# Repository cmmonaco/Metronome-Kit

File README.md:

# Metronome Kit

This barebones metronome was designed as a kit which was sold on Club Jameco (discontinued). Features include a small speaker, flashing LED, and the ability to switch between several different time signature options. The kit includes a three digit seven-segment display to display the speed in beats per minute and runs off of three AA batteries.

Details for the build can be found on [Instructables](https://www.instructables.com/id/Electronic-Metronome/). 

## Bill of Materials
- ATmega328p Microcontroller (Jameco #2139111)
- IC Socket (Jameco #112300)
- 150 Ohm Resistor (Jameco #690662)
- 10k Ohm Resistor (Jameco #691104)
- 0.1 uF Capacitor (Jameco #151116)
- Three Digit Seven Segment Display (Jameco #1956493)
- Red 5mm LED (Jameco #333973)
- Tactile Switch (3x) (Jameco #119011)
- Piezo Speaker (Jameco #1874543)
- ISP Header (Jameco #115035)
- 3xAA Battery Holder with Switch (Jameco #216144)
- AA Battery (3x)
- Velcro (Optional)

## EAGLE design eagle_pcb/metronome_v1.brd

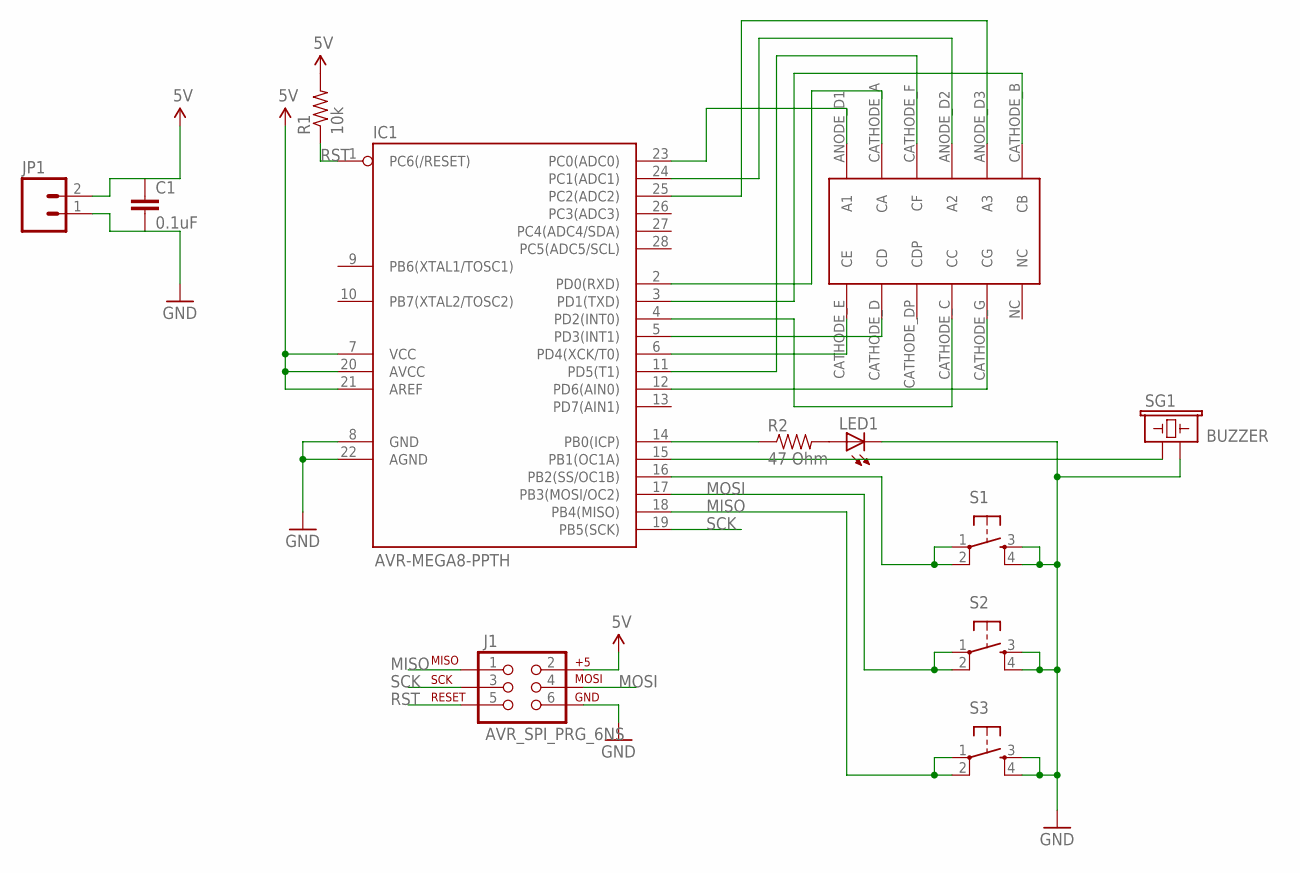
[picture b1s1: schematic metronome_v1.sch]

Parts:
C1: 0.1uF; CAP-PTH-SMALL
IC1: AVR-MEGA8-PPTH; DIL28-3
J1: AVR_SPI_PRG_6NS; 2X3-NS
JP1: M02PTH3; 1X02_LONGPADS
LED1: LED5MM
R1: 10k; AXIAL-0.3
R2: 47 Ohm; AXIAL-0.3
S1, S2, S3: TAC_SWITCHPTH; TACTILE-PTH
SG1: BUZZER; BUZZER-762MM
U$1: 7-SEGMENT-3DIGIT-LTC516R; 7-SEGMENT-3DIGIT-LTC561R

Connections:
5V: C1.1, IC1.7 (VCC), IC1.20 (AVCC), IC1.21 (AREF), J1.2, JP1.2, R1.P$2 (2)
GND: C1.2, IC1.8 (GND), IC1.22 (AGND), J1.6, JP1.1, LED1.K (C), S1.3, S1.4, S2.3, S2.4, S3.3, S3.4, SG1.P$2 (2)
MISO: IC1.18 (PB4(MISO)), J1.1, S3.1, S3.2
MOSI: IC1.17 (PB3(MOSI/OC2)), J1.4, S2.1, S2.2
unnamed: LED1.A, R2.P$2 (2)
unnamed: IC1.14 (PB0(ICP)), R2.P$1 (1)
unnamed: IC1.2 (PD0(RXD)), U$1.CATHODE_A (CA)
unnamed: IC1.3 (PD1(TXD)), U$1.CATHODE_B (CB)
unnamed: IC1.15 (PB1(OC1A)), SG1.P$1 (1)
unnamed: IC1.16 (PB2(SS/OC1B)), S1.1, S1.2
unnamed: IC1.4 (PD2(INT0)), U$1.CATHODE_C (CC)
unnamed: IC1.5 (PD3(INT1)), U$1.CATHODE_D (CD)
unnamed: IC1.6 (PD4(XCK/T0)), U$1.CATHODE_E (CE)
unnamed: IC1.11 (PD5(T1)), U$1.CATHODE_F (CF)
unnamed: IC1.12 (PD6(AIN0)), U$1.CATHODE_G (CG)
unnamed: IC1.23 (PC0(ADC0)), U$1.ANODE_D1 (A1)
unnamed: IC1.24 (PC1(ADC1)), U$1.ANODE_D2 (A2)
unnamed: IC1.25 (PC2(ADC2)), U$1.ANODE_D3 (A3)
RST: IC1.1 (PC6(/RESET)), J1.5, R1.P$1 (1)
SCK: IC1.19 (PB5(SCK)), J1.3

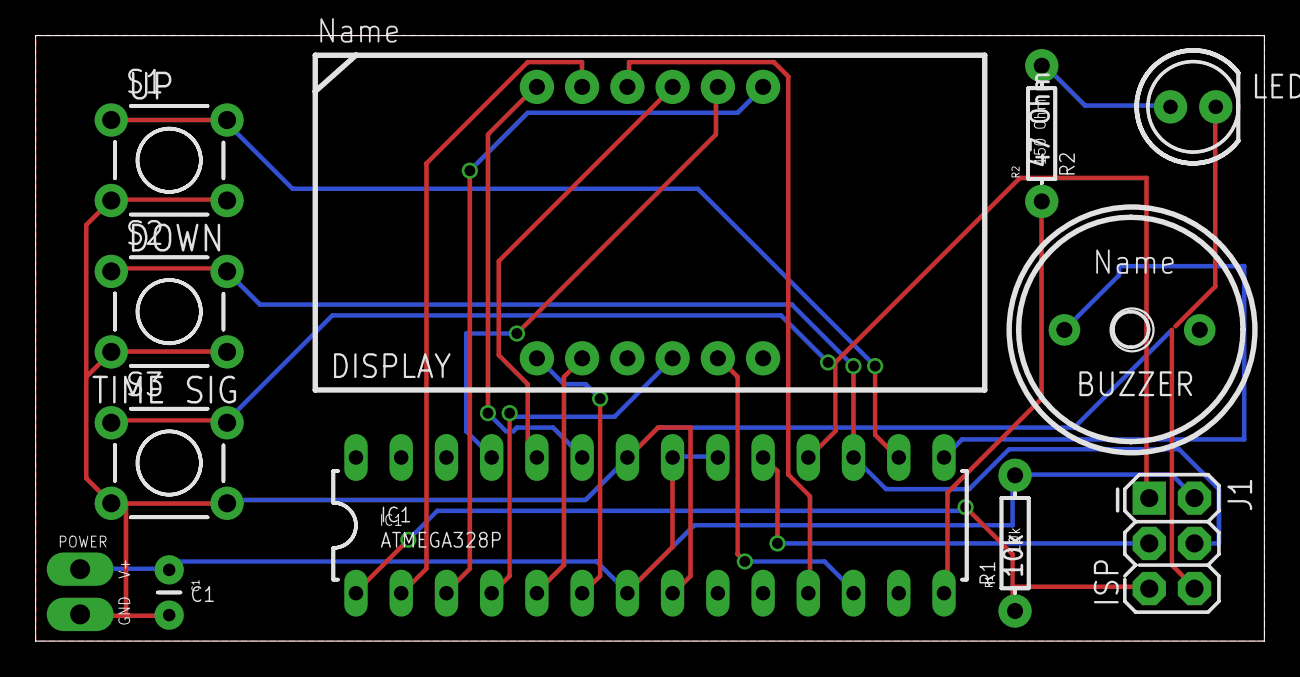
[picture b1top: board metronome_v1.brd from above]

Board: 2 copper layers, 69.0 x 34.0 mm, 12 parts (0 on the bottom side), 20 nets.

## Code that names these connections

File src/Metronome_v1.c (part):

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#define MAX_SPEED              250   //Max metronome speed in BPM
#define MIN_SPEED              30    //Min metronome speed in BPM

#define DISP_CATH_PORT         PORTD //The Display cathodes are connected to pins PD0-PD6
#define DISP_AN_PORT           PORTC //The Display anodes are connected to pins PC0-PC2
#define DIGIT1                 0     //PC0
#define DIGIT2                 1     //PC1
#define DIGIT3                 2     //PC2
#define OUTPUT_PORT            PORTB //The Buzzer is connected to pin PB1/OCA1, LED is connected to PB0

#define INPUT                  PINB  //Buttons are on PB2-PB4
#define LED_PIN                0     //PB0
#define DEBOUNCE_COUNT_MAX     240    //Number used for debouncing the buttons
#define TIMESIG_DISPLAY_LENGTH 500  //Number of loops during which to display the current time signature

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{
	//Handle Pin Direction Settings
	DDRD = 0xFF; //DISP_CATH_PORT, set all pins as output
	DDRC = 0x07; //DISP_AN_PORT, set pins PC0, PC1, PC2 as output
	DDRB = 0x03; //I/O pins on port B, set pins 0 and 1 as output
	PORTB = 0x1C; //Set internal pull-ups on pins PB2, PB3, PB4
	
	//Initialize iCounterMax for tone generation
	iCounterMax = toneFreq*((float)60/(float)speed);
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
/************************************************************************/
/* ISR(TIMER1_COMPA_vect)                                               */
/* Used to turn on and off the PWM on pin PB1 so that tone only sounds  */
/* on beats. Also flashes an LED.                                       */
/************************************************************************/
ISR(TIMER1_COMPA_vect)
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	/*
	This is where the actual operation of the metronome occurs! Back in
	setup() function we started Timer1 in fast PWM mode. This toggles
	pin PB1 at rate we also specified. In addition to toggling the pin,
	this interrupt is fired. If the PB1 toggling function is always 
	enabled we would hear a constant tone from the speaker. This is of
	no use for a metronome, so instead we only turn the toggling 
	functionality on for a short time at each beat so the we get a short
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	cannot see the on and off and instead see a constant LED.
	*/
	iCounter++; //increment interrupt counter
	TCCR1A &= ~(1<<COM1A0); //disable PWM output on pin PB1
	
	if((iCounter == iCounterMax) || buzzerflag == 1)
	{			
		buzzerflag = 1; //set buzzer flag to on
		OUTPUT_PORT ^= (1<<LED_PIN); //toggle LED
		TCCR1A |= (1<<COM1A0); //enable PWM output on pin PB1
		
		//if the buzzer has been on for the specified length of time
		if(iCounter == (iCounterMax + buzzPeriod))
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

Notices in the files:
src/Metronome_v1.c:
Copyright (c) 2012 Chris Monaco
All rights reserved.
parts and their libraries:
SparkFun-Displays: Licensing: CC v3.0 Share-Alike You are welcome to use this library for commercial purposes.
